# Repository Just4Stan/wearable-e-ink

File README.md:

# Wearable-E-Ink
A beginner-friendly soldering workshop project to build a WiFi-enabled, programmable e-paper name badge. This project is designed to be completed in a 2-3 hour session, teaching participants how to solder both through-hole and surface-mount (SMD) components.

Initial designed to give workshops at HighTechLab in Leuven

# Block Diagram

(AI generated for simple overview)
See the kicad files for schematics and PCB design

# Display

See datasheet for "GDEM0154Z91" 

# CAD

OnShape: https://cad.onshape.com/documents/da012de4a02ab2054a0e627e/w/e4c4a902931b74520d1464dc/e/3234466a68d54d344f0d976d?renderMode=0&uiState=68dfa4af8854ede9226c917d

# Features
- ESP8266 Powered: Uses the powerful ESP-12F module for WiFi connectivity and control.
- High-Contrast Display: Features a 1.54-inch, 200x200 pixel black and white e-paper screen.
- Beginner-Friendly Design: The PCB is laid out with "progressive difficulty," starting with easy components to build confidence before moving to more challenging SMD parts.
- USB-C Connectivity: Modern, robust connector for power and programming.
- Web Updatable: Firmware supports updating the display content via a simple web API over WiFi.
- Fully Open Source: The hardware design and firmware are free to use, modify, and distribute.

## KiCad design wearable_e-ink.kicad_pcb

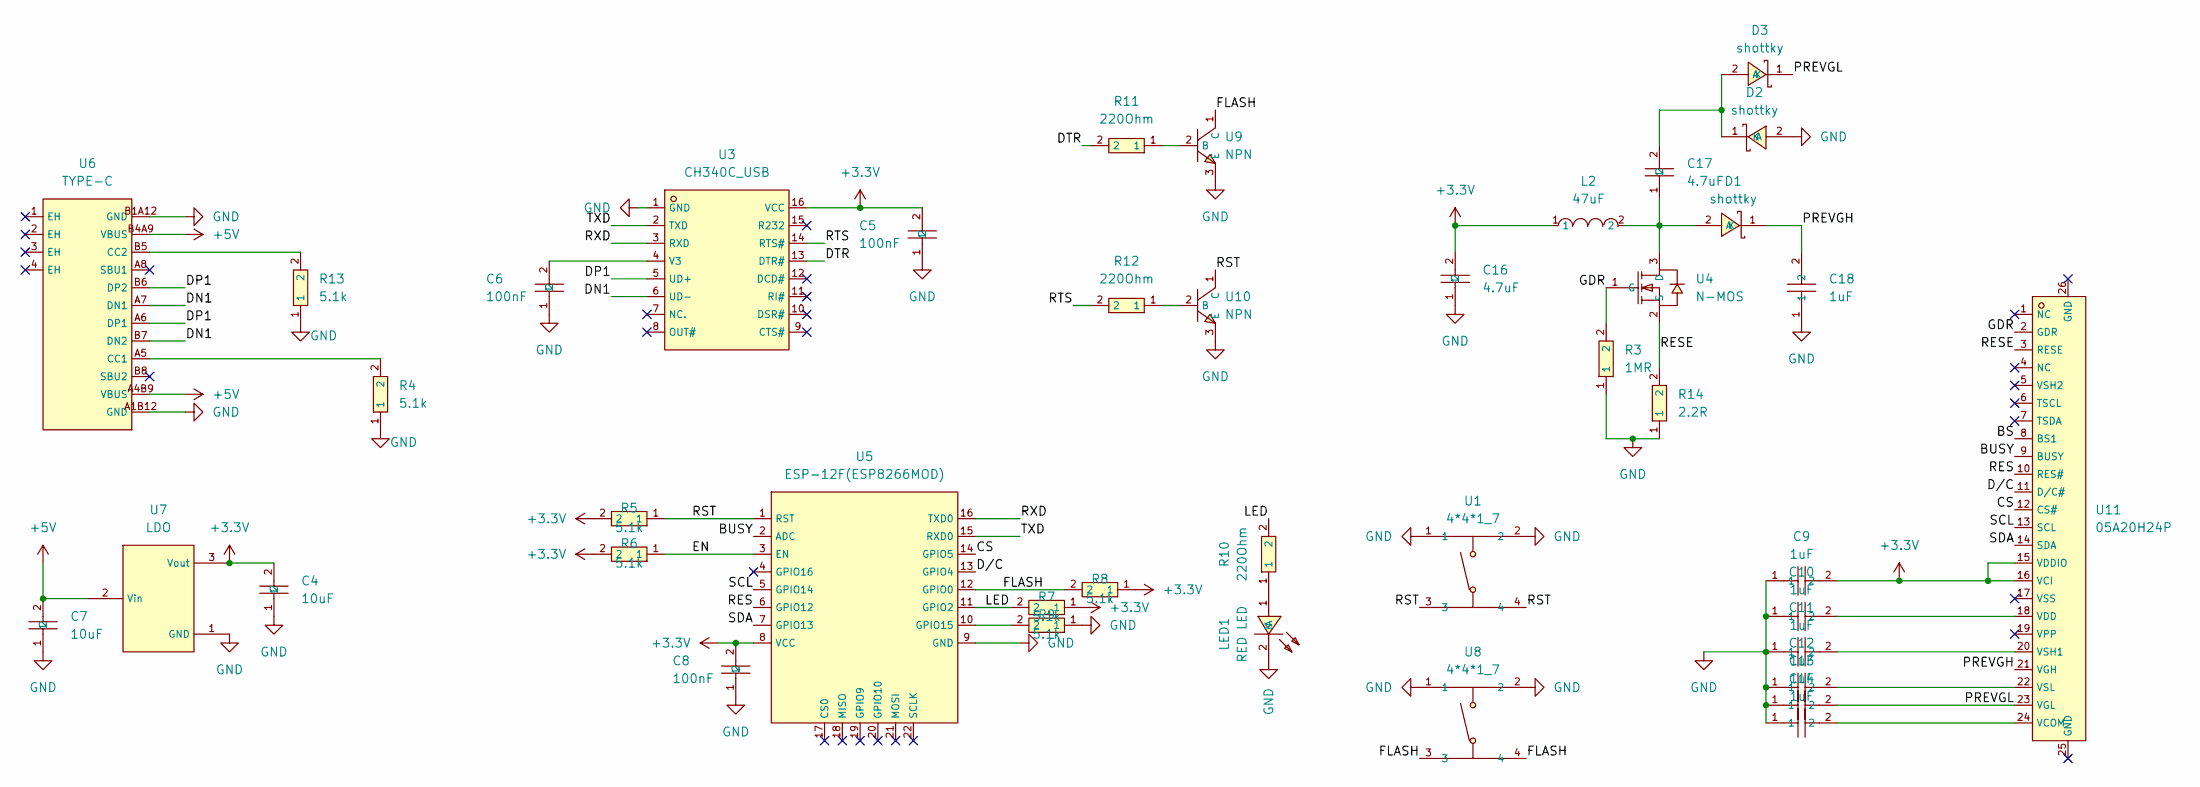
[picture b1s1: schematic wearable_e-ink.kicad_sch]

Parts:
C4, C7: 10uF; C1206; LCSC C1849
C5, C6, C8: 100nF; C1206; LCSC C1945
C9, C10, C11, C12, C13, C14, C18: 1uF; C1206; LCSC C1848
C16, C17: 4.7uF; C1206; LCSC C1872
D1, D2, D3: shottky; SOD-123_L2.8-W1.8-LS3.7-RD; LCSC C18863
L2: 47uF; IND-SMD_L4.0-W4.0; LCSC C76869
LED1: RED LED; LED1206-R-RD_RED; LCSC C49018
R3: 1MR; R1206; LCSC C17927
R4, R5, R6, R7, R8, R9, R13: 5.1k; R1206; LCSC C26033
R10, R11, R12: 220Ohm; R1206; LCSC C17957
R14: 2.2R; R1206; LCSC C17947
U1, U8: 4*4*1_7; SW-SMD_4P-L5.2-W5.2-P3.70-LS6.5; LCSC C10852
U3: CH340C_USB; SOP-16_L10.0-W3.9-P1.27-LS6.0-BL; LCSC C7464026
U4: N-MOS; SOT-23-LDO; LCSC C2588
U5: ESP-12F(ESP8266MOD); WIFIM-SMD_ESP-12F-ESP8266MOD; LCSC C82891
U6: TYPE-C; USB-C_SMD-TYPE-C-31-M-12_1; LCSC C165948
U7: LDO; SOT-23-LDO; LCSC C5446
U9, U10: NPN; SOT-23-LDO; LCSC C8533
U11: 05A20H24P; FPC-SMD_24P-P0.50_05A20H24P; LCSC C5362175

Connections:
+3.3V: C4.2, C5.2, C8.2, C9.2, C16.2, L2.1, R5.2, R6.2, R7.1, R8.1, U3.16 (VCC), U5.8 (VCC), U7.3 (Vout), U11.15 (VDDIO), U11.16 (VCI)
+5V: C7.2, U6.A4B9 (VBUS), U6.B4A9 (VBUS), U7.2 (Vin)
/BS: U11.8 (BS1)
/BUSY: U5.2 (ADC), U11.9 (BUSY)
/CS: U5.14 (GPIO5), U11.12 (CS#)
/DN1: U3.6 (UD-), U6.A7 (DN1), U6.B7 (DN2)
/DP1: U3.5 (UD+), U6.A6 (DP1), U6.B6 (DP2)
/DTR: R11.2, U3.13 (DTR#)
/D/C: U5.13 (GPIO4), U11.11 (D/C#)
/EN: R6.1, U5.3 (EN)
/FLASH: R8.2, U5.12 (GPIO0), U8.3, U8.4, U9.1 (C)
/GDR: R3.2, U4.1 (G), U11.2 (GDR)
/LED: R7.2, R10.2, U5.11 (GPIO2)
/PREVGH: C18.2, D1.1 (K), U11.21 (VGH)
/PREVGL: C13.2, D3.1 (K), U11.23 (VGL)
/RES: U5.6 (GPIO12), U11.10 (RES#)
/RESE: R14.2, U4.2 (S), U11.3 (RESE)
/RST: R5.1, U1.3, U1.4, U5.1 (RST), U10.1 (C)
/RTS: R12.2, U3.14 (RTS#)
/RXD: U3.3 (RXD), U5.16 (TXD0)
/SCL: U5.5 (GPIO14), U11.13 (SCL)
/SDA: U5.7 (GPIO13), U11.14 (SDA)
/TXD: U3.2 (TXD), U5.15 (RXD0)
GND: C4.1, C5.1, C6.1, C7.1, C8.1, C9.1, C10.1, C11.1, C12.1, C13.1, C14.1, C16.1, C18.1, D2.2 (A), LED1.2 (K), R3.1, R4.1, R9.1, R13.1, R14.1, U1.1, U1.2, U3.1 (GND), U5.9 (GND), U6.A1B12 (GND), U6.B1A12 (GND), U7.1 (GND), U8.1, U8.2, U9.3 (E), U10.3 (E)
unnamed: C17.1, D1.2 (A), L2.2, U4.3 (D)
unnamed: C17.2, D2.1 (K), D3.2 (A)
unnamed: LED1.1 (A), R10.1
unnamed: C6.2, U3.4 (V3)
unnamed: R9.2, U5.10 (GPIO15)
unnamed: R4.2, U6.A5 (CC1)
unnamed: R13.2, U6.B5 (CC2)
unnamed: R11.1, U9.2 (B)
unnamed: R12.1, U10.2 (B)
unnamed: C14.2, U11.24 (VCOM)
unnamed: C10.2, U11.18 (VDD)
unnamed: C11.2, U11.20 (VSH1)
unnamed: C12.2, U11.22 (VSL)

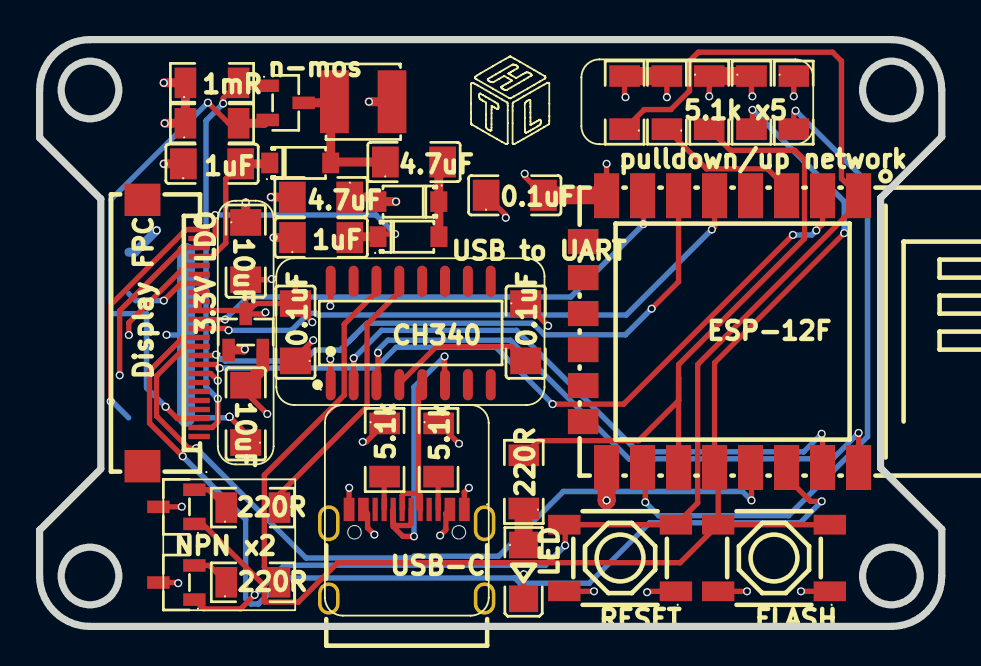
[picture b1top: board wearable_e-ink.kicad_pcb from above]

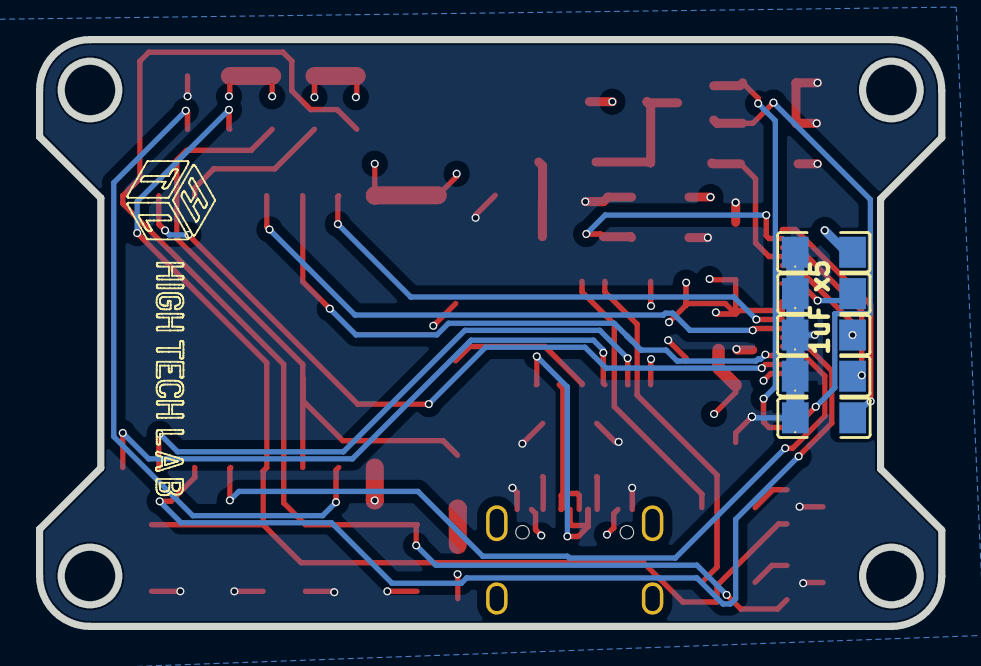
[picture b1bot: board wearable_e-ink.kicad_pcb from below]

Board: 4 copper layers, 50.1 x 32.6 mm, 41 parts (5 on the bottom side), 36 nets.

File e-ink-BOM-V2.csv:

"Reference","Value","Footprint","Datasheet","Qty","DNP","Exclude from BOM","Exclude from Board"
"C4,C7","10uF","wearable-e-inks:C1206","https://item.szlcsc.com/89171.html","2","","",""
"C5,C6,C8","100nF","wearable-e-inks:C1206","https://item.szlcsc.com/89171.html","3","","",""
"C9,C10,C11,C12,C13,C14,C18","1uF","wearable-e-inks:C1206","https://item.szlcsc.com/89171.html","7","","",""
"C16,C17","4.7uF","wearable-e-inks:C1206","https://item.szlcsc.com/89171.html","2","","",""
"D1,D2,D3","shottky","wearable-e-inks:SOD-123_L2.8-W1.8-LS3.7-RD","https://item.szlcsc.com/301422.html","3","","",""
"L2","47uF","wearable-e-inks:IND-SMD_L4.0-W4.0","https://item.szlcsc.com/109498.html","1","","",""
"LED1","RED LED","wearable-e-inks:LED1206-R-RD_RED","https://item.szlcsc.com/73803.html","1","","",""
"R3","1MR","wearable-e-inks:R1206","https://item.szlcsc.com/311874.html","1","","",""
"R4,R5,R6,R7,R8,R9,R13","5.1k","wearable-e-inks:R1206","https://item.szlcsc.com/311874.html","7","","",""
"R10,R11,R12","220Ohm","wearable-e-inks:R1206","https://item.szlcsc.com/311874.html","3","","",""
"R14","2.2R","wearable-e-inks:R1206","https://item.szlcsc.com/311874.html","1","","",""
"U1,U8","4*4*1_7","wearable-e-inks:SW-SMD_4P-L5.2-W5.2-P3.70-LS6.5","https://lcsc.com/product-detail/Tactile-Switches_BOOMELE-Boo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","2","","",""
"U3","CH340C_USB","wearable-e-inks:SOP-16_L10.0-W3.9-P1.27-LS6.0-BL","https://item.szlcsc.com/391677.html","1","","",""
"U4","N-MOS","wearable-e-inks:SOT-23-LDO","https://item.szlcsc.com/236142.html","1","","",""
"U5","ESP-12F(ESP8266MOD)","wearable-e-inks:WIFIM-SMD_ESP-12F-ESP8266MOD","https://item.szlcsc.com/84052.html","1","","",""
"U6","TYPE-C","wearable-e-inks:USB-C_SMD-TYPE-C-31-M-12_1","https://item.szlcsc.com/datasheet/TYPE-C-31-M-12/177331.html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","1","","",""
"U7","LDO","wearable-e-inks:SOT-23-LDO","https://item.szlcsc.com/14454.html","1","","",""
"U9,U10","NPN","wearable-e-inks:SOT-23-LDO","https://www.diodes.com/assets/Package-Files/SOT23.pdf","2","","",""
"U11","05A20H24P","wearable-e-inks:FPC-SMD_24P-P0.50_05A20H24P","https://atta.szlcsc.com/upload/public/pdf/source/20230308/DA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","1","","",""

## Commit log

2025-10-02 First schematic rev and component selection
2025-10-02 added BOM
2025-10-02 First pcb design layout
2025-10-03 Switched out daughter board for on-board FPC and display signal conditioning. First of V2
2025-10-03 added display datasheet
2025-10-03 added CAD
2025-10-03 Final V2 Exports
